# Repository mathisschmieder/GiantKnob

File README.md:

# GiantKnob
USB-Midi-Controller for SDR Radios

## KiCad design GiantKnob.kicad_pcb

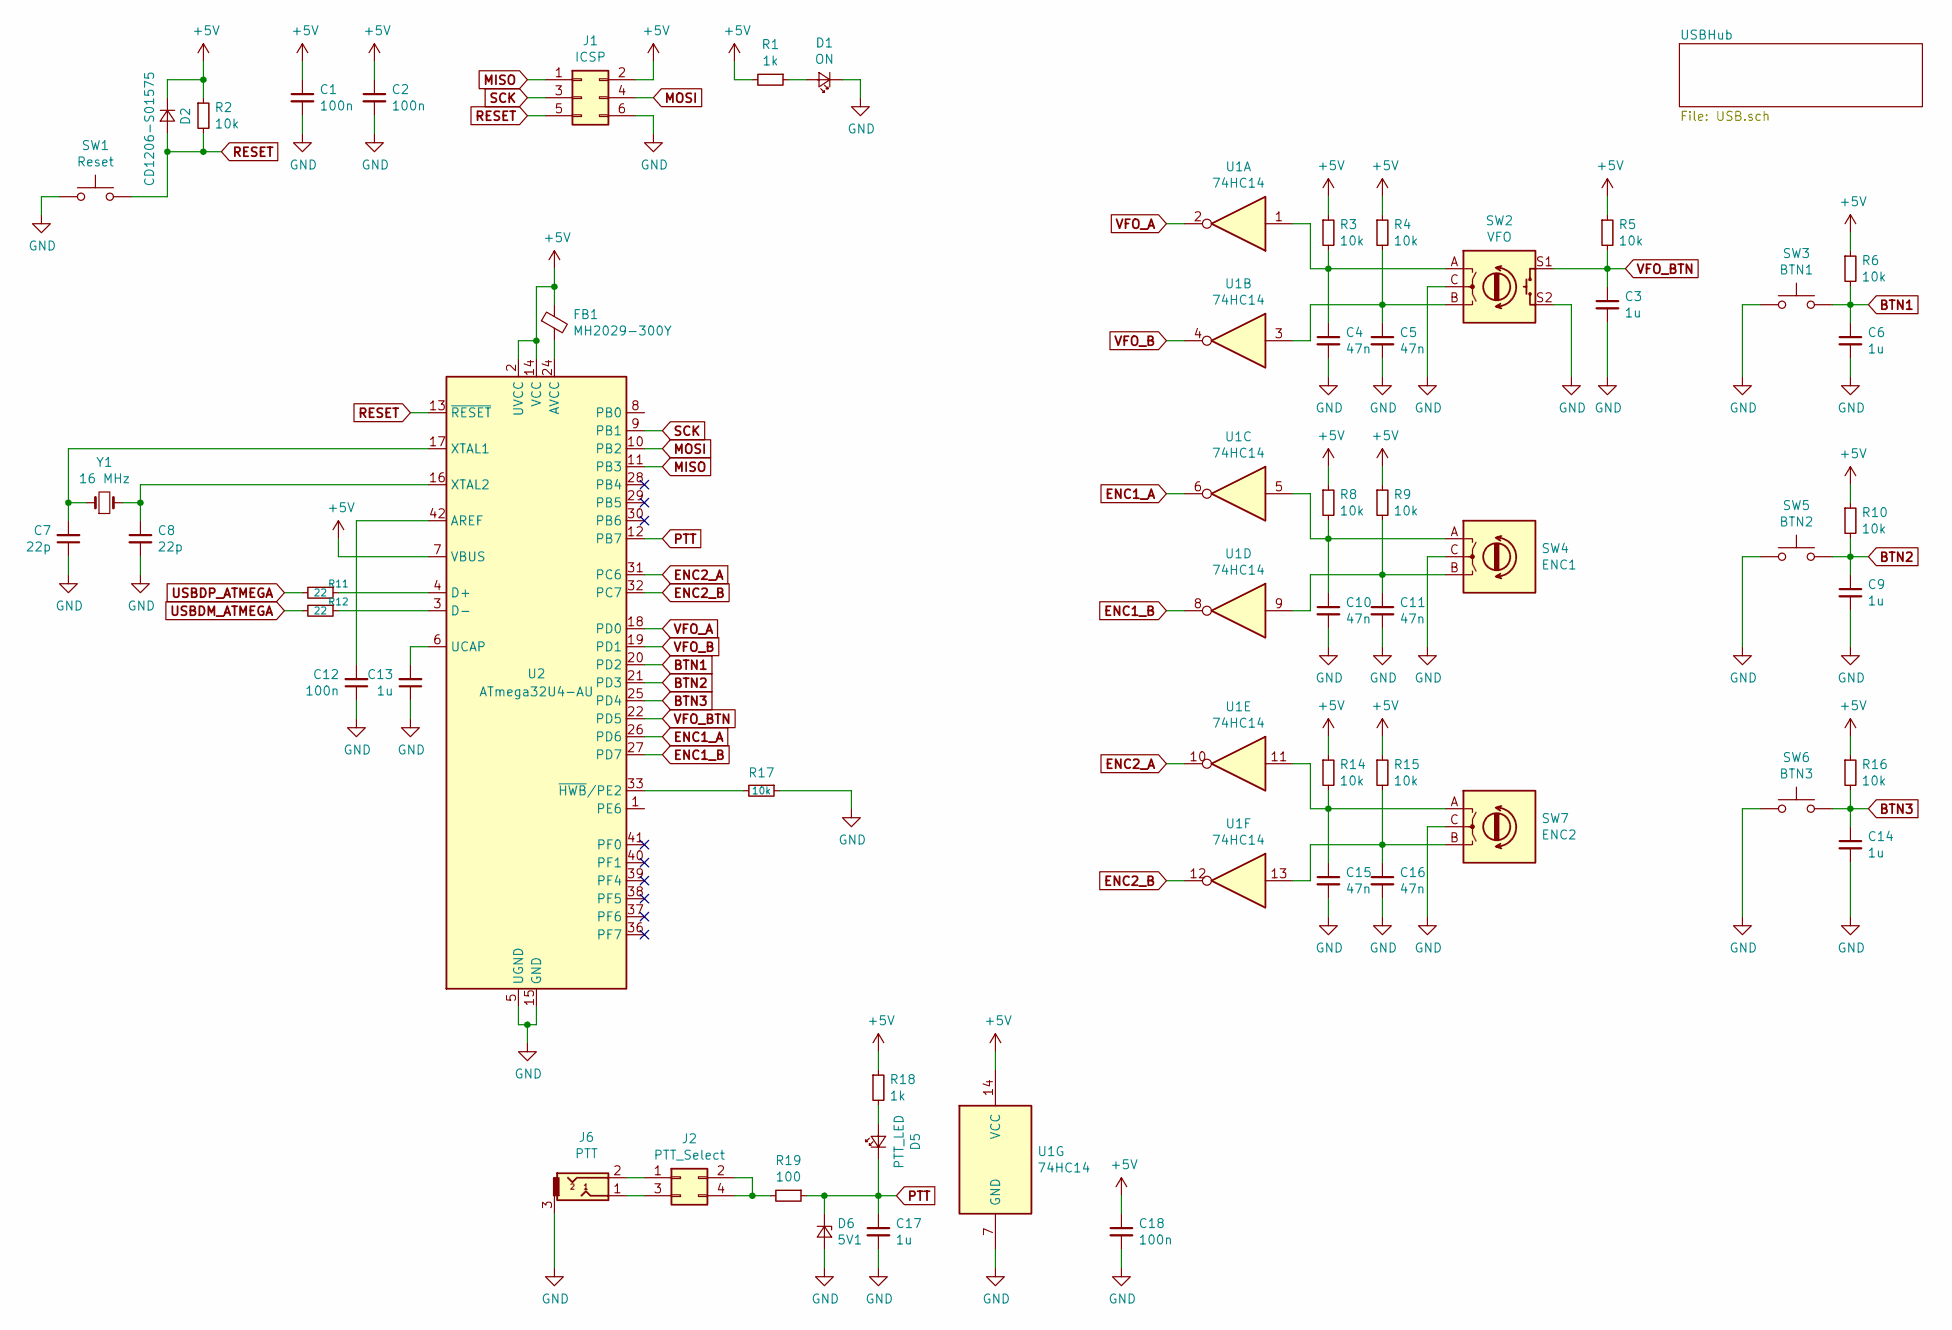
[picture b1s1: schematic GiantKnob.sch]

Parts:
C1, C2, C12, C18: 100n; C_0603_1608Metric
C3, C6, C9, C13, C14, C17: 1u; C_0603_1608Metric
C4, C5, C10, C11, C15, C16: 47n; C_0603_1608Metric
C7, C8: 22p; C_0603_1608Metric
D1: ON; LED_0805_2012Metric
D2: CD1206-S01575; D_1206_3216Metric
D5: PTT_LED; LED_0805_2012Metric
D6: 5V1; D_SOD-123
FB1: MH2029-300Y; L_0805_2012Metric
J1: ICSP; PinHeader_2x03_P2.54mm_Vertical_SMD
J2: PTT_Select; PinHeader_2x02_P2.54mm_Vertical_SMD
J6: PTT; PJ-320B
R1, R18: 1k; R_0603_1608Metric
R2, R3, R4, R5, R6, R8, R9, R10, R14, R15, R16, R17: 10k; R_0603_1608Metric
R11, R12: 22; R_0603_1608Metric
R19: 100; R_0603_1608Metric
SW1: Reset; SW_SPST_PTS645
SW2: VFO; RotaryEncoder_Alps_EC12E-Switch_Vertical_H20mm
SW3: BTN1; SW_PUSH-12mm
SW4: ENC1; RotaryEncoder_Alps_EC12E_Vertical_H20mm
SW5: BTN2; SW_PUSH-12mm
SW6: BTN3; SW_PUSH-12mm
SW7: ENC2; RotaryEncoder_Alps_EC12E_Vertical_H20mm
U1: 74HC14; SOIC-14_3.9x8.7mm_P1.27mm
U2: ATmega32U4-AU; TQFP-44_10x10mm_P0.8mm
Y1: 16 MHz; Crystal_SMD_5032-2Pin_5.0x3.2mm

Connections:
+5V: C1.1, C2.1, C18.1, D2.1 (K), FB1.1, J1.2, R1.2, R2.1, R3.1, R4.1, R5.1, R6.1, R8.1, R9.1, R10.1, R14.1, R15.1, R16.1, R18.1, U1.14 (VCC), U2.2 (UVCC), U2.7 (VBUS), U2.14 (VCC), U2.34 (VCC); also elsewhere on the board
BTN1: C6.1, R6.2, SW3.2, U2.20 (PD2)
BTN2: C9.1, R10.2, SW5.2, U2.21 (PD3)
BTN3: C14.1, R16.2, SW6.2, U2.25 (PD4)
ENC1_A: U1.6, U2.26 (PD6)
ENC1_B: U1.8, U2.27 (PD7)
ENC2_A: U1.10, U2.31 (PC6)
ENC2_B: U1.12, U2.32 (PC7)
GND: C1.2, C2.2, C3.2, C4.2, C5.2, C6.2, C7.1, C8.2, C9.2, C10.2, C11.2, C12.1, C13.1, C14.2, C15.2, C16.2, C17.2, C18.2, D1.1 (K), D6.2 (A), J1.6, J6.3, R17.1, SW1.1, SW2.C, SW2.S2, SW3.1, SW4.C, SW5.1, SW6.1, SW7.C, U1.7 (GND), U2.5 (UGND), U2.15 (GND), U2.23 (GND), U2.35 (GND), U2.43 (GND); also elsewhere on the board
MISO: J1.1, U2.11 (PB3)
MOSI: J1.4, U2.10 (PB2)
unnamed: C4.1, R3.2, SW2.A, U1.1
unnamed: C5.1, R4.2, SW2.B, U1.3
unnamed: C7.2, U2.17 (XTAL1), Y1.1
unnamed: C8.1, U2.16 (XTAL2), Y1.2
unnamed: C10.1, R8.2, SW4.A, U1.5
unnamed: C11.1, R9.2, SW4.B, U1.9
unnamed: C12.2, U2.42 (AREF)
unnamed: C13.2, U2.6 (UCAP)
unnamed: C15.1, R14.2, SW7.A, U1.11
unnamed: C16.1, R15.2, SW7.B, U1.13
unnamed: D1.2 (A), R1.1
unnamed: D5.2 (A), R18.2
unnamed: FB1.2, U2.24 (AVCC), U2.44 (AVCC)
unnamed: J2.1, J6.2
unnamed: J2.2, J2.4, R19.2
unnamed: J2.3, J6.1
unnamed: R11.1, U2.4 (D+)
unnamed: R12.1, U2.3 (D-)
unnamed: R17.2, U2.33 (~HWB~/PE2)
PTT: C17.1, D5.1 (K), D6.1 (K), R19.1, U2.12 (PB7)
RESET: D2.2 (A), J1.5, R2.2, SW1.2, U2.13 (~RESET)
SCK: J1.3, U2.9 (PB1)
USBDM_ATMEGA: R12.2; also elsewhere on the board
USBDP_ATMEGA: R11.2; also elsewhere on the board
VFO_A: U1.2, U2.18 (PD0)
VFO_B: U1.4, U2.19 (PD1)
VFO_BTN: C3.1, R5.2, SW2.S1, U2.22 (PD5)

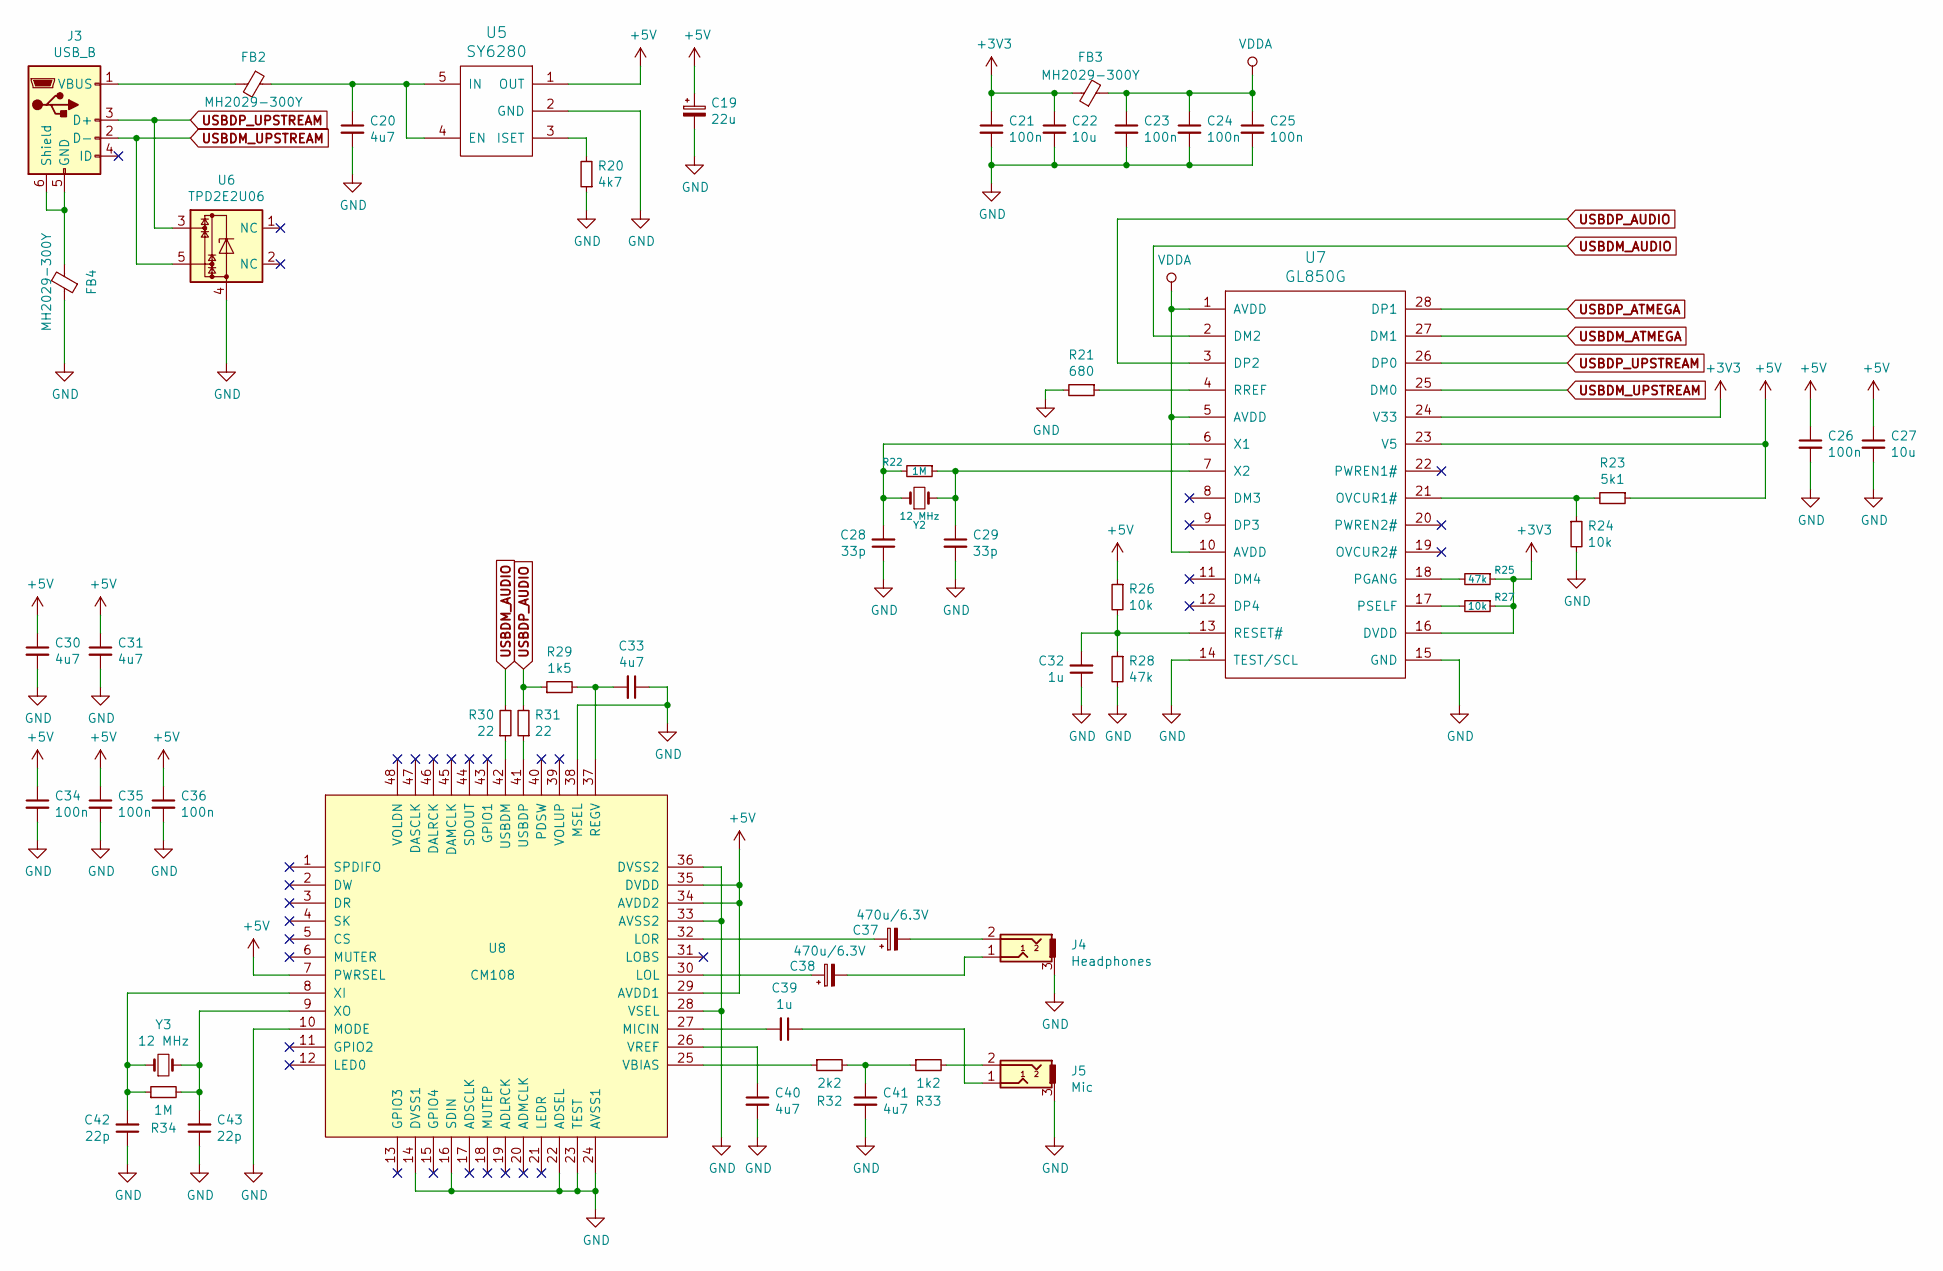
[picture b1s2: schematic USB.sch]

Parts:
C19: 22u; CP_EIA-3216-18_Kemet-A
C20, C30, C31, C33, C40, C41: 4u7; C_0603_1608Metric
C21, C23, C24, C25, C26, C34, C35, C36: 100n; C_0603_1608Metric
C22, C27: 10u; C_0603_1608Metric
C28, C29: 33p; C_0603_1608Metric
C32, C39: 1u; C_0603_1608Metric
C37, C38: 470u/6.3V; CP_EIA-7343-31_Kemet-D
C42, C43: 22p; C_0603_1608Metric
FB2, FB3, FB4: MH2029-300Y; L_0805_2012Metric
J3: USB_B; USB_Mini-B_Lumberg_2486_01_Horizontal
J4: Headphones; PJ-320B; LCSC PJ-320B
J5: Mic; PJ-320B; LCSC PJ-320B
R20: 4k7; R_0603_1608Metric
R21: 680; R_0603_1608Metric
R22, R34: 1M; R_0603_1608Metric
R23: 5k1; R_0603_1608Metric
R24, R26, R27: 10k; R_0603_1608Metric
R25, R28: 47k; R_0603_1608Metric
R29: 1k5; R_0603_1608Metric
R30, R31: 22; R_0603_1608Metric
R32: 2k2; R_0603_1608Metric
R33: 1k2; R_0603_1608Metric
U5: SY6280; SOT-23-5
U6: TPD2E2U06; SOT-553
U7: GL850G; SSOP-28_5.3x10.2mm_P0.65mm
U8: CM108; LQFP-48_7x7mm_P0.5mm
Y2, Y3: 12 MHz; Crystal_SMD_5032-2Pin_5.0x3.2mm

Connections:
+3V3: C21.1, C22.1, FB3.1, R25.1, R27.1, U7.16 (DVDD), U7.24 (V33)
+5V: C19.1, C26.1, C27.1, C30.1, C31.1, C34.1, C35.1, C36.1, R23.1, R26.1, U5.1 (OUT), U7.23 (V5), U8.7 (PWRSEL), U8.29 (AVDD1), U8.34 (AVDD2), U8.35 (DVDD); also elsewhere on the board
GND: C19.2, C20.2, C21.2, C22.2, C23.2, C24.2, C25.2, C26.2, C27.2, C28.1, C29.2, C30.2, C31.2, C32.1, C33.1, C34.2, C35.2, C36.2, C40.2, C41.2, C42.1, C43.1, FB4.1, J4.3, J5.3, R20.1, R21.2, R24.2, R28.2, U5.2 (GND), U6.4, U7.14 (TEST/SCL), U7.15 (GND), U8.10 (MODE), U8.14 (DVSS1), U8.16 (SDIN), U8.22 (ADSEL), U8.23 (TEST), U8.24 (AVSS1), U8.28 (VSEL), U8.33 (AVSS2), U8.36 (DVSS2), U8.38 (MSEL); also elsewhere on the board
unnamed: C20.1, FB2.1, U5.4 (EN), U5.5 (IN)
unnamed: C28.2, R22.2, U7.6 (X1), Y2.1
unnamed: C29.1, R22.1, U7.7 (X2), Y2.2
unnamed: C32.2, R26.2, R28.1, U7.13 (RESET#)
unnamed: C33.2, R29.2, U8.37 (REGV)
unnamed: C37.1, U8.32 (LOR)
unnamed: C37.2, J4.2
unnamed: C38.1, U8.30 (LOL)
unnamed: C38.2, J4.1
unnamed: C39.1, J5.1
unnamed: C39.2, U8.27 (MICIN)
unnamed: C40.1, U8.26 (VREF)
unnamed: C41.1, R32.2, R33.1
unnamed: C42.2, R34.1, U8.8 (XI), Y3.1
unnamed: C43.2, R34.2, U8.9 (XO), Y3.2
unnamed: FB2.2, J3.1 (VBUS)
unnamed: FB4.2, J3.5 (GND), J3.6 (Shield)
unnamed: J5.2, R33.2
unnamed: R20.2, U5.3 (ISET)
unnamed: R21.1, U7.4 (RREF)
unnamed: R23.2, R24.1, U7.21 (OVCUR1#)
unnamed: R25.2, U7.18 (PGANG)
unnamed: R27.2, U7.17 (PSELF)
unnamed: R30.1, U8.42 (USBDM)
unnamed: R31.1, U8.41 (USBDP)
unnamed: R32.1, U8.25 (VBIAS)
USBDM_ATMEGA: U7.27 (DM1); also elsewhere on the board
USBDM_AUDIO: R30.2, U7.2 (DM2)
USBDM_UPSTREAM: J3.2 (D-), U6.5, U7.25 (DM0)
USBDP_ATMEGA: U7.28 (DP1); also elsewhere on the board
USBDP_AUDIO: R29.1, R31.2, U7.3 (DP2)
USBDP_UPSTREAM: J3.3 (D+), U6.3, U7.26 (DP0)
VDDA: C23.1, C24.1, C25.1, FB3.2, U7.1 (AVDD), U7.5 (AVDD), U7.10 (AVDD)

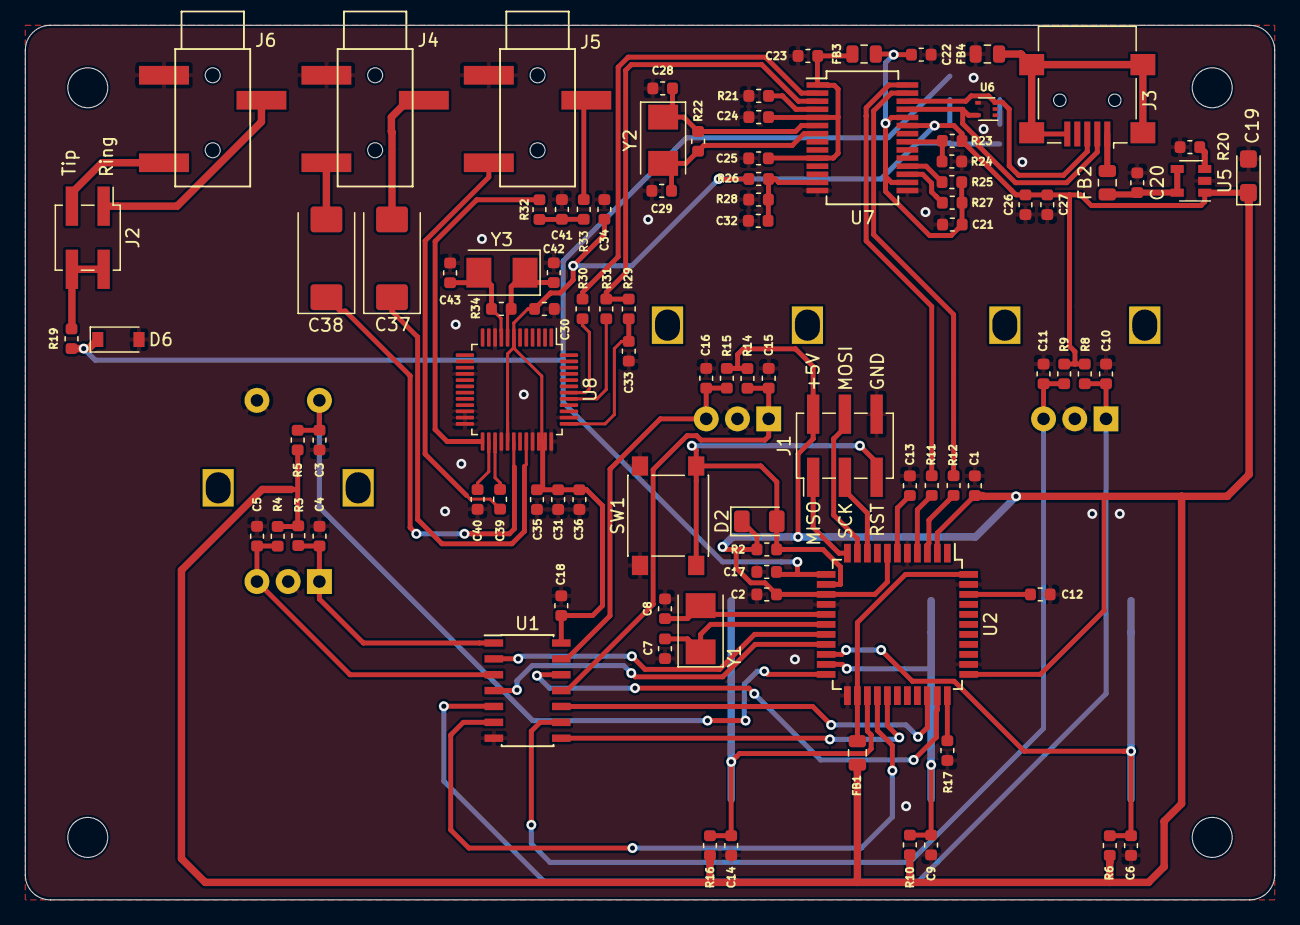
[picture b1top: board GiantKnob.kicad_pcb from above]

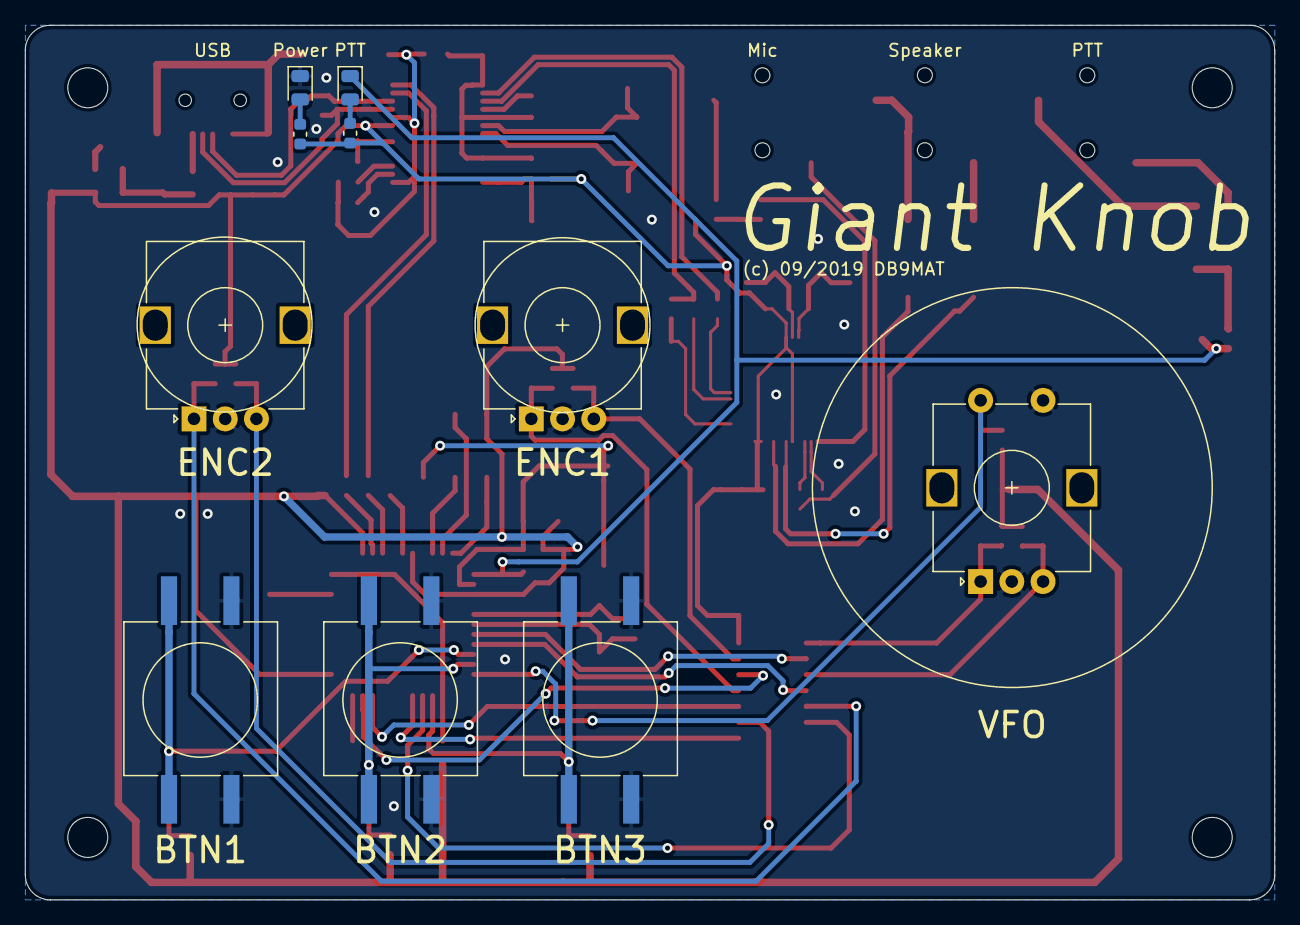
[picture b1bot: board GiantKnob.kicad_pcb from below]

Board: 2 copper layers, 100.0 x 70.0 mm, 105 parts (10 on the bottom side), 70 nets.

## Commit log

2019-09-17 First version of schematics
2019-09-17 Added PTT to ATmega32U4
2019-09-17 Added component footprints
2019-09-18 Board layout for prototype
2019-09-23 Prototype v1
